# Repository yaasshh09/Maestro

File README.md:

# Maestro
 
A compact 6-key macropad with a rotary encoder and OLED display, built around the Seeeduino XIAO RP2040 and running QMK firmware. Small footprint, fully custom, and 3D printed.

## Overview
 
This is a 6-key macropad arranged in a 2x3 matrix, with a rotary encoder for analog-style control and a 0.91" OLED for live feedback. It is built on a custom PCB, with the Seeeduino XIAO RP2040 socketed on top. It runs QMK, so every key, layer, and encoder action is fully remappable, and you get access to the entire QMK feature set (layers, tap-dance, macros, combos.
 
The whole thing is housed in a 3D printed case designed to hold the PCB, switches, encoder, OLED, and XIAO board in place.

## Features
 
- 6 mechanical switches wired in a 2x3 matrix
- Rotary encoder with push-button
- 0.91" OLED display for layer and status readout
- Seeeduino XIAO RP2040 microcontroller
- Runs QMK firmware with full layer and macro support
- Custom designed PCB with socketed XIAO RP2040
- 3D printed three-part case

## Bill of Materials
|Amount|Part|
|-|-|
|1x|Seeeduino XIAO RP2040|
|6x|MX-style switches|
|6x|1N4148 diodes|
|1x|EC11 rotary encoder + knob|
|1x|0.91" SSD1306 OLED (I2C, 4-pin)|
|1x|custom PCB|
|1x|3D printed case (top + plate + base)|
|1x|USB-C cable|
 
## FIRMWARE (QMK)
### 1. Set up QMK

If you haven't already, install QMK and its toolchain:

```bash
qmk setup
```

On Windows, run all *qmk* commands inside the *QMK MSYS* terminal that is
installed with QMK.

### 2. Link this keyboard into your QMK tree

Clone this repo, then link `qmk_firmware/keyboards/maestro` to the keyboard
folder here. 

**Useful scripts:**

**Windows**:

```powershell
cd Firmware\Link
.\link-keyboard.ps1                                  
```
*or :*
```powershell
.\link-keyboard.ps1 -QmkHome "D:\path\to\qmk_firmware"
```

### 3. Build
```bash
qmk compile -kb maestro -km default
```

The compiled maestro_default.uf2 is written to the root of your qmk_firmware folder.

### 4. Flash

Put the XIAO RP2040 into bootloader mode. Either drag the `.uf2` onto that drive, or run:

```bash
qmk flash -kb maestro -km default
```

## OLED Display
 
The 0.91" OLED can show whatever you program in `oled_task_user()`. Common uses:
 
- Current active layer
- Caps/lock status
- A logo or small animation
- Encoder mode indicator

*Keep in mind the 128x32 resolution is small, so stick to short text or compact bitmaps.*

## OLED Companion App

OLED Display cant fetch data itself (keyboard has no internet). A Small external companion app runs on the host computer, reads current Spotify track, pushes to pad over raw HID through app.

- Spotify playing: OLED shows song and artist.
- Spotify idle: OLED shows current time and date.

Firmware just displays what the app sends.

**Requires RAW_ENABLE = yes in rules.mk.**
 
---   
 
## CAD

3D printed, three stacked layers:

- Base layer: tray with raised perimeter wall, four corner screw posts, USB-C notch on side. Houses PCB, secured with screws through corner posts.

- Plate layer: flat sheet with six square switch cutouts in 2x3 grid and raised border wall. Fixed with single screw at bottom, plus optional superglue for extra hold.

- Top layer: frame with large open window to showcase PCB, dedicated cutout slot for OLED and rotary encoder, screw hole, chamfered corners.

---

## Notes
 
- Match your matrix and encoder pins in keyboard.json / config.h to the PCB routing before flashing.
- If the OLED does not light up, confirm the I2C address (usually 0x3C) and the header orientation.
- If the keys ghost or repeat, check diode placement and matrix definitions.

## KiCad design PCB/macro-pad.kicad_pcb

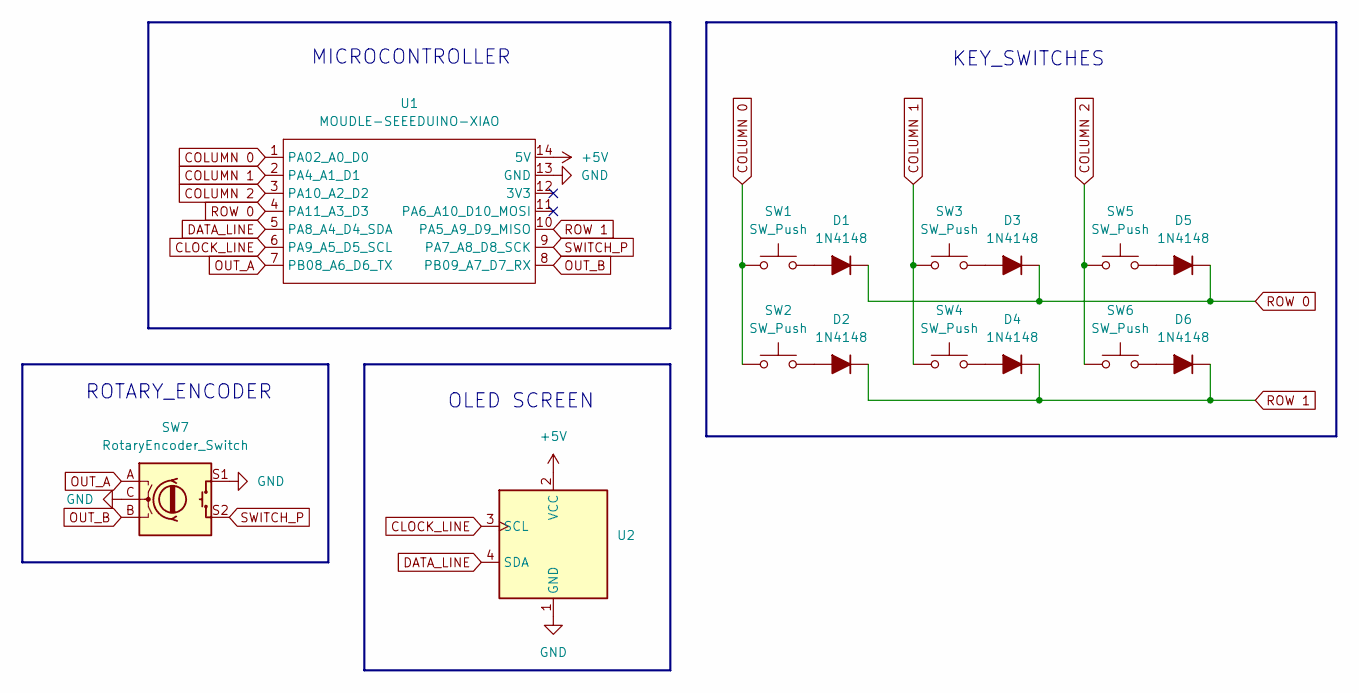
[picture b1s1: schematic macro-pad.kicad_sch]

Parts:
D1, D2, D3, D4, D5, D6: 1N4148; D_DO-35_SOD27_P7.62mm_Horizontal
SW1, SW2, SW3, SW4, SW5, SW6: SW_Push; MX-Solderable-1U
SW7: RotaryEncoder_Switch; RotaryEncoder_Alps_EC11E-Switch_Vertical_H20mm
U1: MOUDLE-SEEEDUINO-XIAO; XIAO-Generic-Hybrid-14P-2.54-21X17.8MM
U2: ER_OLEDM0.91_1x-I2C

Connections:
+5V: U1.14 (5V), U2.2 (VCC)
CLOCK_LINE: U1.6 (PA9_A5_D5_SCL), U2.3 (SCL)
COLUMN 0: SW1.1, SW2.1, U1.1 (PA02_A0_D0)
COLUMN 1: SW3.1, SW4.1, U1.2 (PA4_A1_D1)
COLUMN 2: SW5.1, SW6.1, U1.3 (PA10_A2_D2)
DATA_LINE: U1.5 (PA8_A4_D4_SDA), U2.4 (SDA)
GND: SW7.C, SW7.S1, U1.13 (GND), U2.1 (GND)
unnamed: D1.2 (A), SW1.2
unnamed: D2.2 (A), SW2.2
unnamed: D3.2 (A), SW3.2
unnamed: D4.2 (A), SW4.2
unnamed: D5.2 (A), SW5.2
unnamed: D6.2 (A), SW6.2
OUT_A: SW7.A, U1.7 (PB08_A6_D6_TX)
OUT_B: SW7.B, U1.8 (PB09_A7_D7_RX)
ROW 0: D1.1 (K), D3.1 (K), D5.1 (K), U1.4 (PA11_A3_D3)
ROW 1: D2.1 (K), D4.1 (K), D6.1 (K), U1.10 (PA5_A9_D9_MISO)
SWITCH_P: SW7.S2, U1.9 (PA7_A8_D8_SCK)

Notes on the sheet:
MICROCONTROLLER
OLED SCREEN
KEY_SWITCHES
ROTARY_ENCODER

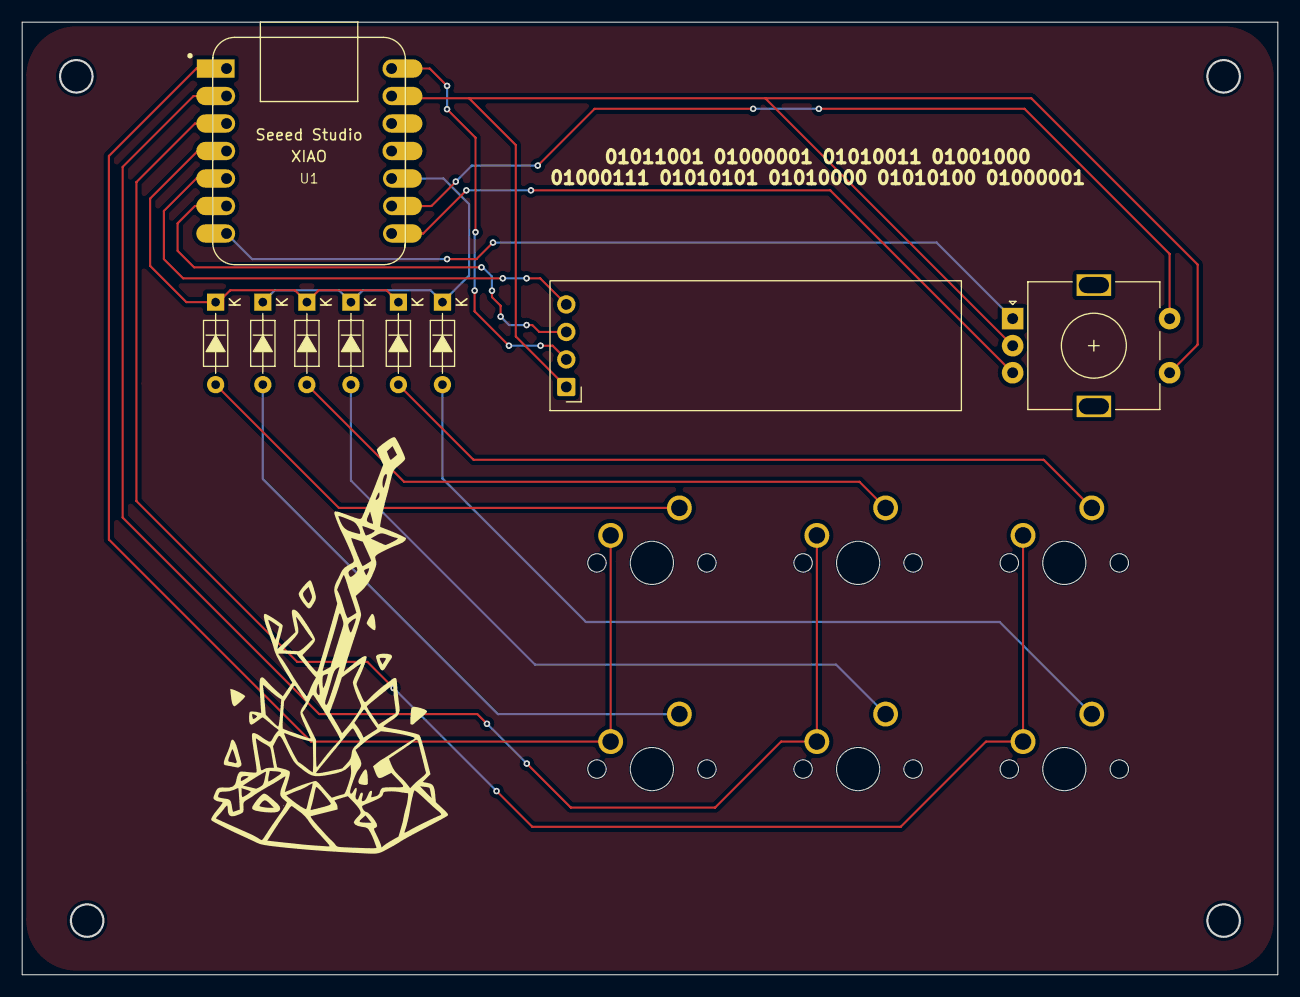
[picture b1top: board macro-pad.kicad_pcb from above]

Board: 2 copper layers, 116.0 x 88.0 mm, 15 parts (0 on the bottom side), 18 nets.

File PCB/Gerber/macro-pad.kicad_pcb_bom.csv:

Designator,Quantity,Value,Footprint,Package,MPN,DNP,Mount_Type,Description
"D1, D2, D3, D4, D5, D6",6,1N4148,D_DO-35_SOD27_P7.62mm_Horizontal,,,,tht,"DO-35 Diode, Small Signal, Fast Switching, 75V, 150mA, 4ns, Alternate KiCad Library"
"SW1, SW2, SW3, SW4, SW5, SW6",6,SW_Push,MX-Solderable-1U,,,,tht,"Push button switch, generic, two pins"
SW7,1,RotaryEncoder_Switch,RotaryEncoder_Alps_EC11E-Switch_Vertical_H20mm,,,,tht,"Rotary encoder, dual channel, incremental quadrate outputs, with switch"
U1,1,MOUDLE-SEEEDUINO-XIAO,XIAO-Generic-Hybrid-14P-2.54-21X17.8MM,,,,smt,
U2,1,ER_OLEDM0.91_1x-I2C,ER_OLEDM0.91_1x-I2C,,,,tht,"SSD1306 OLED module, 0.91 inch, 128x32, I2C"

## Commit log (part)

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2026-06-29 Initial commit of my folder
2026-06-30 Added KiCad Files
